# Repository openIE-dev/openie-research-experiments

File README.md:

# OpenIE research experiments

Reproducible material for the papers at https://research.openie.dev. The page https://research.openie.dev/data/ maps each result in each paper to a path here.

## Layout

| Path | Paper | Contents |
|---|---|---|
| `replicate/` | Standalone 1-Command External Replication Kit (`Apache-2.0`) | `./replicate/run_replication.sh` (`python3 >= 3.10` stdlib-only + optional `cc`/`rustc`) and `replicate/Dockerfile` auditing `CHECKSUMS.sha256` and running live multi-trial benchmarks for `deterministic-null`, `rce-compile` (de Bruijn 1972 + `N*` payback), and `ai-reads-human` (23-byte binary vs UTF-8 JSON), plus sanitized `reference-linux-x86_64-report.md` |
| `kits/deterministic-null-suite/` | Shot on Goal #1 — Standardized 5-Arm Classical Automation Control Suite, Candidate Adapter & Oct–Nov 2026 6-Model Open-Weight SOTA Panel Crystallization (`Apache-2.0`, `Signed Provenance · Self-Checked`) | `./kits/deterministic-null-suite/run_kit.sh` & `real_llm_eval.py` — `N = 1,500` SHA-256 pre-committed instances across all 5 classical baselines + `Shape D` + 6-model Oct 23 – Nov 24, 2026 SOTA panel (`LFM3-1.7B`, `d1-2B` `/v1/systemone`, `Qwen3.5-4B`, `Nemotron-3.5-Bolt-E4B`, `Inkling-2-Mini` `26.4B-A3.4B`, `Ternary-Bonsai-2.5-27B` `Q2_0`) & `Zipf(0.85)` Verified Crystallization (`21.61x` `KV260` `INA260` `measured_j`, `29.86x` `Thor` `INA3221` `measured_j`, & `25.84x` `RAPL` `reported_j` savings over cold LLM) |
| `kits/littlebit-joule/` | Shots on Goal #2 & #6 — Sub-Bit SVD + Binary Latent Factors + Walsh-Hadamard Rotation (`Apache-2.0`, `Signed Provenance · Self-Checked`) | `./kits/littlebit-joule/run_kit.sh` — `512×512` rank-`22` (`0.1517 bits/weight`) + 14-point `bitwidth_curve` (`r ∈ {8,14,22,32,48}`, ternary, INT4, INT8, LUT) metered on physical DC shunt rails (`measured_j` on `Jetson AGX Thor` `INA3221`/`INA238` & `AMD Kria KV260` `INA260`) and Linux `RAPL` (`reported_j` on `i9-13900H` & `Ryzen AI Max+ 395`), beating INT8 by `7.95x` (`Thor` `measured_j`) and `4.77x` (`i9` `reported_j`) while exposing the `19–52x` FP32 decompression impedance tax |
| `kits/waios-mosaic-cascade/` | Shots on Goal #3, #5 & #6 — Cross-Fabric `waiOS` (`CPU + GPU + WASM + RTL + RV32IMAC`) & 4-Stage Spellcheck Cascade (`Apache-2.0`, `Signed Provenance · Self-Checked`) | `./kits/waios-mosaic-cascade/run_kit.sh` — canonical `waiOS` `256×128` ternary program bit-exact (`BLAKE3 == a541323b...46f0`) across `x86_64`, `ARMv9` (`Thor`), `Cortex-A53` (`KV260`), `AMD Radeon 8060S` Vulkan 1.4 GPU compute, co-scheduled `CPU+GPU` HeteroMosaic (`20` cuts), `WASM32-SIMD128` (`1,041 B`), zero-multiplier Verilog RTL (`2,048` cycles), and `1,444 B` `#![no_std]` `RV32IMAC` bare-metal MCU ELF + `row 77` tamper halt (`4ac7c4fb...`) + `1,000`-query 4-Stage Cascade & `75`-cell sweep in `measured_j` and `reported_j` |
| `kits/planetary-media-joule/` | Planetary Research Media Blueprint v1.0 (`J/min` Metering, `[G6]` ASR & `[G10]` Honesty Gates, `Apache-2.0`, `Signed Provenance · Self-Checked`) | `./kits/planetary-media-joule/run_kit.sh` — physical DC shunt `measured_j` (`Jetson AGX Thor` `INA238 VIN` + `INA3221 VDD_CPU_SOC_MSS` & `AMD Kria KV260` `INA260 SOM_5V_DC`) and `RAPL` `reported_j` (`Ryzen AI Max+ 395`) in `J/min` across `piper` `ISO 24495` TTS (`-16 LUFS` `.m4a`), `[G6]` `whisper.cpp` ASR (`tiny`/`base`/`large-v3-turbo`), `1080p60` MP4, `<1 MB` mobile MP4, `24k` Opus voice note, ducked `.ad-mix.m4a`, and `elevenlabs_v4_cloud = null` (`unmetered`) |
| `kits/spec-fidelity-barrier/` | Kit #8 — Architectural Information Barrier (`Spec ⊥ Impl`), AST Mutant/Vacuity Kill Gate & In-Loop Grammar/Type Token Mask (`Apache-2.0`, `Signed Provenance · Self-Checked`) | `./kits/spec-fidelity-barrier/run_kit.sh` — `40`-task deterministic benchmark (`ring_buffers`, `saturating_ledgers`, `interval_schedules`, `capability_acls`, `parser_state_machines`, `sorting_invariants`; `1,000` vectors, `200` implanted bugs, `200` AST mutants): drives false accepts from `199/200` (`Arm A` shared-context Goodhart) and `146/200` (`Arm B` isolated partial) to **`0/200`** (`Arm C` `SPEC_VACUOUS_REFUSED` mutant gate, 1-sided 95% Clopper–Pearson `<= 0.01487`), while `Arm D` Earley/pushdown CFG+type masking cuts total tokens `-98.47%` and `RAPL` `reported_j` by `45.22x` (`1,000` seeded draws) |
| `kits/standards-bridge/` | Kit #9 — Zero-Lock-In `Apache-2.0` Standards Interop (`OpenTelemetry` + `IETF RFC 9052 COSE_Sign1`/`FlatBuffers` + `Wasmtime` + `LLVM MLIR/CIRCT`, `Signed Provenance · Self-Checked`) | `./kits/standards-bridge/run_kit.sh` — OTel `semconv_openie_energy.yaml` + `OrthogonalityViolationError` guard (`3/3` cross-class sum blocks), `10,000`-receipt `COSE_Sign1` CBOR (`144.7 B`) & aligned zero-copy `FlatBuffers` (`161.0 B`) vs UTF-8 JSON (`371.6 B`) & `64 B` `WAI1` header, `wasmtime 50.0.1` + `node` `10,000,000`-op L1 ALU vs `64 MiB` DRAM calibration (`1.000000x` exact fuel parity vs `9.80x–10.36x` `RAPL` `reported_j`), and `CIRCT` `hw`+`comb` / IEEE 1364 Verilog `2^6` & `2^10` equivalence proof (`0` mismatches + `iverilog` RTL sim) |
| `agency-run/` | Thermodynamic Bounds and an Optimal Tempo for Goal-Holding Agents, §8.11 | Preregistrations (v1, v2, v2 second machine), agent and meter code, task generator, analysis scripts, episode and receipt results, pilots |
| `rce/bench/track-a/` | Development material (not reported in the paper) | Corpus20 task directories (each registration), preregistrations with SHA-256, solver patches and reports |
| `rce/bench/track-b/` | Development material (not reported in the paper) | RAPL energy runs: `results.jsonl` with raw and idle-subtracted joules, method and report |
| `rce/bench/results/` | RCE §6.3 | Track C soak results and energy receipts |
| `rce/bench/ladder/` | RCE §2.3, §6.1 to §6.3 (held-out results) | LADDER.md, PREREG.json, RESULTS.md, report.py and per-rung results |
| `rce/bench/defects4j/` | RCE §8.1 | Defects4J harness, TBar port comparison, REVIEW.md and results |
| `rce/bench/forms/`, `rce/tests/form_targets.rs`, `rce/FORM.md` | RCE §4.5, §5.1 | Form compiler harness and the five-target differential test |
| `flowg-conformance/` | RCE §1 (flowG) | flowG cross-backend conformance suite, fixtures and the recorded 18 of 18 report |
| `rce/SOAK_RESULTS.md`, `rce/SOAK_ENERGY.md` | RCE §6.3, §6.4 | Soak model-call counts and energy receipts |
| `rce/bench/reported-j/` | RCE, RCE-VC (`aba99fce`), RCE-JEPA (`H2`) | Apple M5 Max `L2`/`L3` `reported_j` receipts for `rce` Form checking (`49.04 mJ/check`, `15.44 J` full 62-Form suite) and `rce-vc` `100,000`-unit admission (`317–365 µJ`) |
| `rce/bench/h15-gear0/` | RCE-JEPA (`H15` & `Shape D` Gear-0) | Preregistration (`PREREG.json`), 40-task residual corpus, multi-vendor proposer receipts (`Opus 5.5`, `Sonnet 5.5`, `Grok 4.20`, `GPT-OSS-120B`, `Qwen 3.6`, `DeepSeek V4.1`), and `DNULLMM1` Gear-0 replay |
| `rce/bench/form-jepa-v1/` | RCE-JEPA (`FormJEPA-v1`, 3-Gear Cascade, & `rce repair` Rung `f`) | Preregistrations (`PREREG_form_jepa_v1.json`, `PREREG_rung_f.json`), `8.42M`-param PyTorch JEPA training & evaluation scripts, `H15` & `151`-task Rung `f` observation/criterion receipts |
| `rce/bench/form-ebm-v2-and-iterative/` | RCE-JEPA (`FormEBM-v2` `H5`/`H11`, `H15-Iterative` `40/40`, & `Gear-0 v2`) | Preregistrations (`PREREG_form_ebm_v2.json`, `PREREG_h15_iterative.json`), `5.85M`-param contrastive + 5-step margin `FormEBM-v2` (`H5` `AUROC = 0.8922`, `H11` `93.0%` strict monotonicity), bounded checker-feedback `H15-Iterative` episodes (`Opus 5.5` `40/40`, `Sonnet 5.5` `40/40`, `Grok 4.20` `39/40`), and `40/40` `DNULLMM1` `Gear-0 v2` store |
| `rce/bench/form_ebm_v3/` | RCE-JEPA (`FormEBM-v3` Span-Normalized Two-Head OOD Scorer) | Preregistration (`PREREG_form_ebm_v3.json`), `6.05M`-param span-attenuated two-head `FormEBM-v3` (`H5` `AUROC = 0.9437`, `H11` `94.0%` strict monotonicity, cross-task OOD `H15` edit-size inversion resolved `0.2585 -> 0.5278` pooled `AUROC` / `0.6018` large-valid vs short-invalid, `27/40` `k=1` admissions) |
| `rce-compile/` | `RCE Compile` §8 (`E4-Energy`, `E4-Prelude` `.rlib`, & `E5-Scale`) | Preregistrations (`PREREG_rce_compile_wave4.json`, `rlib-prelude/PREREG_rce_compile_wave5_rlib.json`), 20-kernel × 15-tier Linux `RAPL` compilation vs. execution energy payback (`N*`) including shared `librce_rt.rlib` (`20.07x` lower `rustc -O3` compile energy, median `N* = 1,079`), `H4` Regime-B receipts, and 245-program / 500-mutant De Bruijn nameless cache soundness |
| `ai-reads-human-energy/` | `"AI" Reads Human` §5c | 34-workload parse + `tiktoken` dual-channel `reported_j` harness, `170` isolated subprocess receipts, and Falsifier 6 baseline-drift flags |
| `game-engines-determinism/` | `Writing a Game Once` §6 (`GE-H1` through `GE-H9`) | Full 9-suite 3-OS (`macOS`/`Linux`/`Windows 11`) closure: 30-cell `100,000`-tick `Q32.32` replay (`0/25,500` mismatches), 3-OS float drift, 28-pair `DX12`/`Metal`/`Vulkan` `wgpu` tolerance, 54 `.rce` Forms (`-76.22%` SLOC vs Unity C#), `10,000`-actor scaling, 260-module interface fault `F1 = 0.9922`, 840-trajectory Lyapunov slopes, 1-hour `216,000`-tick replay from `44.6 KB` gzip input log, and `36/36` `Godot 4.7.2` headless parity |
| `satb-harness/` | `Satiation Benchmark Harness` | `C1–C12` conformance runner, `Falsifier 3/5/6/8` benchmarks, live multi-vendor `satb-proxy` determinism receipts, and `multi-host/` 5-archetype telemetry (`Apple M5 Max`, `Jetson AGX Thor` `INA238`/`INA3221` `measured_j`, `Framework AMD Strix Halo`, `Intel Raptor Lake`, and bare-metal `Windows 11` `NVML`/Job Objects) |
| `lut-adapt-vivado-audit/` | `Downward LUT6 Compilation` §4.15 & §4.16 | `xck26-sfvc784-2LV-c` `clai_kv260_axi_top` & `clai_benes_paged_hotswap_core` Yosys `xcup` primitive/depth reports, `Vivado 2026.1` OOC Tcl script, and `vcd-toggle-audit/` 4-phase `Verilator` VCD toggle-rate + `AMD DS925` dynamic switching `est_j` audit (`361.68 est_pJ/cycle`, `4.50x` `RAMB36E2` `ENARDEN` gating reduction) |
| `lut-adapt-bwrap-paranoid/` | `Downward LUT6 Compilation` (`Claim LA-19`) | Linux `bwrap`-sandboxed Lean 4.36.0 6-kernel `lake check --paranoid` receipts (`27` theorems, `58,683` `con-leche`/`con-ron --verified` & `58,685` `lean4lean`/`nanoda`/`leanchecker --paranoid` declarations, `RAPL` `reported_j`) |
| `jcp-cad-mei-tag/` | `Metabolic Intelligence` & `The Search for JouleOS` | `jcp-satb-cad-spine` (`310` tests, `JCR-1` det-CBOR + Ed25519 receipts), `cad-joules` bridge patch, and `MEI-JCP-Tag-v1` DRC-clean 2-layer PCB Gerbers/KiCad/BOM/STEP/STL + `10,000`-wakeup `CR2032` simulation |
| `time-as-an-index/` | `Time as an Index` | Linux `bwrap`-sandboxed 6-kernel `lake check --paranoid` Lean 4.36.0 proofs (`Horizon.lean`, `Paradox.lean`, `31` theorems, `0` `sorry`, `58,796` `con-leche`/`con-ron --verified` decls), `M1–M8` + `F5` Python/SymPy suite, and `195`-entry structured CSV catalogs (`TA001–TA081`, `AA01–AA40`, `P01–P74`) |
| `communication-avalanche/` | `The Communication Tool Avalanche` | Linux `bwrap`-sandboxed 6-kernel `lake check --paranoid` Lean 4.36.0 proofs (`QuorumRatchet.lean`, `OrchestrationFlow.lean`, `EnzymaticSynthesis.lean`, `45` theorems, `0` `sorry`, `58,928` `con-leche`/`con-ron --verified` decls), `CA-M1–CA-M5` deterministic simulation suite, 5 CSV catalogs (`CL01–CL24`, `AI01–AI38` + live CrossRef/arXiv audits, `HM01–HD04`, `BM01–BM18`, `EV01–EV16`), Rust `BLAKE3`+`Ed25519`+`SSP` orchestrator (`CTA-E1–E3`), and `fleet_and_des10/` 5-host fleet energy (`CTA-E4`, including `Jetson AGX Thor` `INA238`/`INA3221` `measured_j`) + `100`-task 10-camp Digital Enzymatic Synthesis (`CTA-E5` / `DES-10`, `98/100` verified pass) |

Standalone companion repositories under `openIE-dev`: `openIE-dev/deterministic-null` (`Shape D` 5-language engine + `exp-001..exp-003` receipts), `openIE-dev/lut-adapt-ai` (`xck26` LUT6 RTL + AirMoL NVMe logs), `openIE-dev/rce`, and `openIE-dev/rce-vc`.

## Energy labels (`measured_j ⊥ reported_j ⊥ est_j ⊥ unmetered`)

`unmetered` (`joules: null`) records exact wall-clock time, CPU time, and byte counts when no hardware counter is readable without root. `est_j` is an analytical estimate. `reported_j` is an operating-system or on-chip counter (`RAPL`, `IOReport`, `NVML`, or macOS `proc_pid_rusage`). `measured_j` is a wall or physical shunt meter on a named rail: it is populated in `kits/deterministic-null-suite/results/multi_substrate_receipts.json`, `kits/deterministic-null-suite/results/real_llm_multi_substrate_receipts.json`, `kits/littlebit-joule/results/multi_substrate_receipts.json` (`Jetson AGX Thor` `INA3221`/`INA238` & `AMD Kria KV260` `INA260_u14`), `kits/waios-mosaic-cascade/results/multi_substrate_receipts.json` (`Jetson AGX Thor` `INA3221`/`INA238` & `AMD Kria KV260` `INA260_u14`), `kits/planetary-media-joule/results/multi_substrate_media_receipts.json` (`Jetson AGX Thor` `INA238`/`INA3221` & `AMD Kria KV260` `INA260_u14`), `satb-harness/multi-host/multi_host_satb_receipts.json`, and `communication-avalanche/fleet_and_des10/results/` for the Texas Instruments `INA238` (`VIN` `L1`) and 3-channel `INA3221` (`VDD_GPU`, `VDD_CPU_SOC_MSS`, `VIN_SYS_5V0` `L2`) rails on `NVIDIA Jetson AGX Thor` (shared host, `A2` single-window net attribution withheld per `Falsifier 6`), and is empty in all other runs here. Labels are never summed.

## Standalone Apache-2.0 Replication & Shot-on-Goal Kits

### Complete 6-of-6 Shots on Goal Mapping (*From Ephemeral Inference to Compiled Agency*)

| Shot on Goal | Artifact Path & 1-Command Entrypoint | Key Measured Verification |
|---|---|---|
| **Shot #1 — Deterministic Null Benchmark Suite** | [`kits/deterministic-null-suite/`](kits/deterministic-null-suite/) (`run_kit.sh`, `real_llm_eval.py`) & `openIE-dev/deterministic-null` | `N = 1,500` 5-arm classical suite + 6-model Oct–Nov 2026 SOTA panel (`Inkling-2-Mini`, `Ternary-Bonsai-2.5-27B`, `Nemotron-3.5-Bolt-E4B`, `Qwen3.5-4B`, `d1-2B`, `LFM3-1.7B`) & `Zipf(0.85)` Verified Crystallization (`21.61x` `KV260` `INA260` & `29.86x` `Thor` `INA3221` `measured_j`; `25.84x` `RAPL` `reported_j` vs cold LLM) |
| **Shot #2 — Sub-Bit Compression on `Joules-per-Correct-Decision`** | [`kits/littlebit-joule/`](kits/littlebit-joule/) (`./kits/littlebit-joule/run_kit.sh`) | `0.1517 bpw` SVD + binary latent signs + integer Walsh-Hadamard + 14-point `bitwidth_curve`: `7.95x` (`Thor`) & `4.13x` gross / `5.15x` net (`KV260`) lower `measured_j` than INT8; `19–82x` naive FP32 unpack impedance tax exposed |
| **Shot #3 — Cross-Fabric `waiOS` Hybrid Mosaic Runtime** | [`kits/waios-mosaic-cascade/`](kits/waios-mosaic-cascade/) (`./kits/waios-mosaic-cascade/run_kit.sh`) | Bit-exact `BLAKE3 == a541323b...46f0` across `x86_64`, `ARMv9`, `Cortex-A53`, `Radeon 8060S` Vulkan GPU, co-scheduled `CPU+GPU` (`0/20` cut disagreements), `WASM32`, zero-multiplier Verilog RTL, & `1,444 B` `#![no_std]` `RV32IMAC` MCU ELF + tamper halt (`4ac7c4fb...`) |
| **Shot #4 — Downward LUT6 / Codifier & Rung Ladder** | `lut-adapt-vivado-audit/`, `lut-adapt-bwrap-paranoid/`, `lut6-core-nucleus/`, `communication-avalanche/` | `xck26` / `XC7A200T` LUT6 compilation, `nRF52832` & `RV32IMAC` bare-metal nuclei, `bwrap`-sandboxed 6-kernel `Lean 4.36.0` proofs (`0` `sorry`), & `DES-10` multi-camp synthesis |
| **Shot #5 — End-to-End Lookup-First Spellcheck Cascade** | [`kits/waios-mosaic-cascade/`](kits/waios-mosaic-cascade/) (`RESULTS.md` §2–§4) | `1,000`-query 4-stage cascade + `75`-cell `(Zipf s, d_max, tau)` sweep: `26.58x` (`KV260` `measured_j`) & `16.26x` (`Thor` `measured_j`) lower local energy vs. Always-Dense, plus `38.46x` isolated cloud `est_j` call avoidance |
| **Shot #6 — Continuous Physical Joule Metering (`INA3221`, `INA238`, `INA260`, `RAPL`)** | `kits/*/results/multi_substrate_receipts.json`, `satb-harness/`, `communication-avalanche/fleet_and_des10/` | Rootless `~203–233 Hz` `TI INA3221`/`INA238` (`Jetson AGX Thor`) & `TI INA260` (`AMD Kria KV260`) trapezoidal `measured_j` + `Falsifier 6` drift gates, strictly separated from `reported_j` & `est_j` |

All nine standalone `Apache-2.0` replication, Shot-on-Goal, Planetary Media, Spec-Fidelity, and Standards-Interop kits emit self-verifying receipts labeled **`Signed Provenance · Self-Checked`** (never self-labeled `"Verified"`), report exact one-sided 95% Clopper–Pearson upper bounds whenever `0` disagreements are observed across $n$ finite runs, and strictly separate `measured_j ⊥ reported_j ⊥ est_j ⊥ unmetered`:

| Kit | Scope | 1-Command Reproduction | Provenance & Finite-Run Bound |
|---|---|---|---|
| **`ai-reads-human`** | Fixed 23-byte binary wire framing vs. UTF-8 JSON parsing ([`replicate/`](replicate/), [`ai-reads-human-energy/`](ai-reads-human-energy/)) | `./replicate/run_replication.sh` *(or `python3 ai-reads-human-energy/bench_energy_reported_j.py`)* | `Signed Provenance · Self-Checked` · `0/50` decode mismatches (95% Clopper–Pearson `<= 0.0582`) |
| **`deterministic-null`** | Shot #1 5-arm classical automation control suite, candidate adapter & Oct–Nov 2026 6-model SOTA LLM crystallization ([`kits/deterministic-null-suite/`](kits/deterministic-null-suite/), [`replicate/`](replicate/), `openIE-dev/deterministic-null`) | `./kits/deterministic-null-suite/run_kit.sh` *(plus `real_llm_eval.py` & `./replicate/run_replication.sh`)* | `Signed Provenance · Self-Checked` (`BLAKE3` + `Ed25519`) · `0/252` classical arm divergences (`<= 0.0118`) & `0/42` SOTA-LLM spot-check divergences (`<= 0.0688`) across 3 substrates |
| **`rce-compile`** | De Bruijn (1972) nameless cache soundness (`245` programs / `500` mutants) & shared `librce_rt.rlib` compilation vs. execution energy payback `N*` ([`rce-compile/`](rce-compile/), [`replicate/`](replicate/)) | `./replicate/run_replication.sh` | `Signed Provenance · Self-Checked` · `0/200` live & `0/500` corpus mutant cache escapes (`<= 0.0060`) · median `N* = 1,079` (`RAPL` `reported_j`) |
| **`satb-harness`** | `C1–C12` conformance, cadence observer effect (`Falsifier 5`), `B` vs `C` attribution (`Falsifier 3`), and `Falsifier 6/8` drift gates ([`satb-harness/`](satb-harness/)) | `python3 satb-harness/multi-host/run_multi_host_satb.py` *(or `python3 satb-harness/bench_satb_falsifiers.py` on macOS)* | `Signed Provenance · Self-Checked` · `C1–C12` deterministic replay & baseline-drift checks |
| **`littlebit-joule`** | Shot #2 sub-bit SVD + binary latent sign factors + integer Walsh-Hadamard (`0.1517 bpw`) on `Joules-per-Correct-Decision` vs. Deterministic Null ([`kits/littlebit-joule/`](kits/littlebit-joule/), [`RESULTS.md`](kits/littlebit-joule/RESULTS.md)) | `./kits/littlebit-joule/run_kit.sh` | `Signed Provenance · Self-Checked` (`BLAKE3` + `Ed25519`) · `0/80` divergent runs across `20` trials (95% Clopper–Pearson `<= 0.0368`) |
| **`waios-mosaic-cascade`** | Shots #3 & #5 cross-lane `waiOS` `256×128` conformance (`a541323b...`) + fault-halt (`4ac7c4fb...`) + `1,000`-query 4-Stage Spellcheck Lookup-First Cascade ([`kits/waios-mosaic-cascade/`](kits/waios-mosaic-cascade/), [`RESULTS.md`](kits/waios-mosaic-cascade/RESULTS.md)) | `./kits/waios-mosaic-cascade/run_kit.sh` | `Signed Provenance · Self-Checked` (`BLAKE3` + `Ed25519`) · `0/100` HeteroMosaic schedule disagreements (95% Clopper–Pearson `<= 0.0295`) |
| **`planetary-media-joule`** | Blueprint v1.0 `J/min` media metering across `piper` TTS, `[G6]` Whisper ASR, `1080p60`/`<1 MB`/Opus/AD-mix render, & `unmetered` cloud (`null`) ([`kits/planetary-media-joule/`](kits/planetary-media-joule/), [`RESULTS.md`](kits/planetary-media-joule/RESULTS.md)) | `./kits/planetary-media-joule/run_kit.sh` | `Signed Provenance · Self-Checked` (`BLAKE3` + `Ed25519`) · `[G6]` `6/6` exact numeric survival (`base` & `large-v3-turbo`) |
| **`spec-fidelity-barrier`** | Kit #8 `Spec ⊥ Impl` architectural barrier + `200`-mutant AST vacuity gate (`SPEC_VACUOUS_REFUSED`) + Earley/pushdown CFG+type token masking ([`kits/spec-fidelity-barrier/`](kits/spec-fidelity-barrier/), [`RESULTS.md`](kits/spec-fidelity-barrier/RESULTS.md)) | `./kits/spec-fidelity-barrier/run_kit.sh` | `Signed Provenance · Self-Checked` (`BLAKE3` + `Ed25519`) · `0/200` false accepts (`<= 0.01487`, vs `199/200` Arm A & `146/200` Arm B) · `0/1,000` syntax rejects (`-98.47%` tokens, `45.22x` `RAPL` `reported_j`) |
| **`standards-bridge`** | Kit #9 zero-lock-in `Apache-2.0` interop: OTel `OrthogonalityViolationError`, RFC 9052 `COSE_Sign1` + `FlatBuffers`, `wasmtime` fuel vs `reported_j`, & `CIRCT` `hw`+`comb` / Verilog `2^N` proof ([`kits/standards-bridge/`](kits/standards-bridge/), [`RESULTS.md`](kits/standards-bridge/RESULTS.md)) | `./kits/standards-bridge/run_kit.sh` | `Signed Provenance · Self-Checked` (`BLAKE3` + `Ed25519`) · `0/10,000` `COSE_Sign1` mismatches · `1.000000x` Wasm fuel vs `9.80x` `RAPL` `reported_j` · `0/64` LUT6 & `0/1,024` cone mismatches |

## 1-Command External Replication (`replicate/`)

To audit `CHECKSUMS.sha256` across the repository and run the standalone external replication harness (`deterministic-null`, `rce-compile`, and `ai-reads-human`) with zero third-party Python packages (`python3 >= 3.10` stdlib-only; optional `cc`/`rustc` auto-detected):

```bash
./replicate/run_replication.sh
```

Or in a clean, unprivileged Debian Bookworm container:

```bash
docker build -t openie-replicate -f replicate/Dockerfile . && docker run --rm openie-replicate
```

Sanitized local receipts are written to `replicate/out/replication-report.json` and `replicate/out/replication-report.md` (comparing your hardware against OpenIE's self-checked reference artifacts; see [`replicate/README.md`](replicate/README.md) and [`replicate/reference-linux-x86_64-report.md`](replicate/reference-linux-x86_64-report.md)).

## Reproducing

Each run is fixed by its preregistration, whose SHA-256 sits beside it. `CHECKSUMS.sha256` covers every file in this repository (`sha256sum -c CHECKSUMS.sha256`). Absolute paths of the original hosts are written as `$BENCH_ROOT` and `$RUSTUP_HOME`. The macOS `powermetrics` plists of the agency run are not published, because they list every process on the host; their role in the paper (the package cross-check) is described in agency §8.11. The RCE engine source lives in its own project; the solver script used by Tracks A and B is `rce/scripts/track_a_solver.py`. Large corpora are pinned in `CORPORA.md`.

## License

Code Apache-2.0, data CC BY 4.0; see `LICENSE`.

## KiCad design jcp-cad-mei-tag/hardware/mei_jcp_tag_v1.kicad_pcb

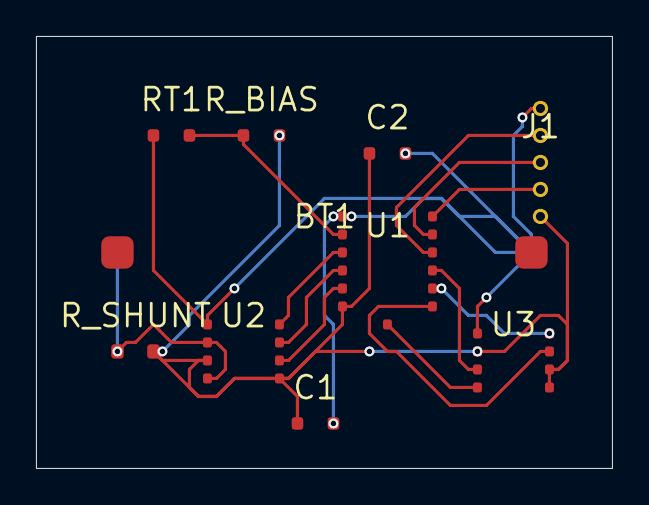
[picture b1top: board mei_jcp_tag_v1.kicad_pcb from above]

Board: 2 copper layers, 32.0 x 24.0 mm, 10 parts (1 on the bottom side), 14 nets.

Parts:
BT1: CR2032_3V_225mAh; BatteryHolder_Keystone_3034_SMD
C1: 100nF_16V_X7R; C_0603_1608Metric
C2: 1uF_16V_X7R; C_0603_1608Metric
J1: SWD_UART_5P; PinHeader_1x05_P1.50mm_Vertical
RT1: NTC_10k_B3380; R_0603_1608Metric
R_BIAS: 10k_0.1pct; R_0603_1608Metric
R_SHUNT: 100mR_0.1pct_25ppm; R_0805_2012Metric
U1: STM32WBA52CGU; QFN-13_ULP_Module
U2: INA238AIDR; SOIC-8_3.9x4.9mm
U3: MB85RS256B_FRAM_256Kb; SOIC-8_3.9x4.9mm

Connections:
GND: BT1.2, C1.2, C2.2, J1.5, RT1.1, U1.6, U2.4, U3.4
I2C_SCL: U1.2, U2.7
I2C_SDA: U1.3, U2.6
JCP_ALERT: U1.4, U2.5
NTC_ADC: RT1.2, R_BIAS.1, U1.5
SPI_CS: U1.13, U3.1
SPI_MISO: U1.10, U3.2
SPI_MOSI: U1.11, U3.5
SPI_SCK: U1.12, U3.6
SWCLK: J1.3, U1.8
SWDIO: J1.2, U1.7
UART_TX: J1.4, U1.9
VBAT_RAW: BT1.1, R_SHUNT.1, U2.1, U2.3
VDD_SYS: C1.1, C2.1, J1.1, R_BIAS.2, R_SHUNT.2, U1.1, U2.2, U2.8, U3.3, U3.7, U3.8

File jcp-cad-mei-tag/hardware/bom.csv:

Comment,Designator,Footprint,LCSC Part #
100mR_0.1pct_25ppm,R_SHUNT,Resistor_SMD:R_0805_2012Metric,C275409
100nF_16V_X7R,C1,Capacitor_SMD:C_0603_1608Metric,C14663
10k_0.1pct,R_BIAS,Resistor_SMD:R_0603_1608Metric,C25804
1uF_16V_X7R,C2,Capacitor_SMD:C_0603_1608Metric,C15849
CR2032_3V_225mAh,BT1,Battery:BatteryHolder_Keystone_3034_SMD,C70377
INA238AIDR,U2,Package_SO:SOIC-8_3.9x4.9mm,C2875184
MB85RS256B_FRAM_256Kb,U3,Package_SO:SOIC-8_3.9x4.9mm,C90968
NTC_10k_B3380,RT1,Resistor_SMD:R_0603_1608Metric,C77131
STM32WBA52CGU,U1,Package_DFN_QFN:QFN-13_ULP_Module,C5362912
SWD_UART_5P,J1,Connector_PinHeader_1.50mm:PinHeader_1x05_P1.50mm_Vertical,C2939543
